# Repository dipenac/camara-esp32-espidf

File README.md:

# Proyecto vision artifical - ESP32CAM

 ## Instrucciones de instalacion y configuracion
 En esta seccion se detalla el proceso de instalacion y configuracion de los repositorios necesarios para el manejo de un **esp32-cam** por medio de el entorno de desarrolo **ESP-IDF**, en el sistema operativo LINUX. 

 ### ESP-IDF
 La instalacion y configuracion del entorno de desarrollo se puede encontrar directamente en el repositorio del fabricante espressif ([Get started - ESPIDF](https://docs.espressif.com/projects/esp-idf/en/latest/esp32/get-started/index.html)).

 - [x] En primer lugar es necesario **clonar el repositorio** de github correspondiente de ESP-IDF.
   ```sh
   git clone --recursive https://github.com/espressif/esp-idf
   ``` 
 - [x] Una vez clonado el repositorio es necesario dirigirse a la carpeta.
   ```sh
   cd ~/esp-idf
   ```
 - [x] Es necesario ejecutar el archivo bash **install.sh**, para poder utilizar las funciones de ESP-IDF.
   ```sh
   ./install.sh
   ``` 
 - [x] Luego se ejecuta el archivo bash **export.sh**, para exportar las variables de entorno que se utilizaran.
   ```sh
   . ./export.sh
   ```
En este punto el entorno de desarrollo ESP-IDF debe estar configurado y listo para implementar proyectos sobre un esp32.

 ### Driver para esp32-cam 
  La instalacion y configuracion del driver se puede encontrar directamente en el repositorio del fabricante espressif ([ESP32 Camera Driver](https://github.com/espressif/esp32-camera)).

 - [x] En primer lugar es necesario **clonar el repositorio** de github correspondiente del driver esp32-cam. Es necesario clonar el repositorio en la carpeta *components* del repositorio clonado de ESP-IDF.
   ```sh
   cd ~/esp-idf/components
   git clone --recursive https://github.com/espressif/esp32-camera
   ``` 
 - [x] Una vez clonado el repositorio en la carpeta correspondiente, se procede a [crear un proyecto](#crear-un-proyecto-esp-idf) en ESP-IDF. Una vez creado el proeycto es necesario realizar los ajustes necesarios para que el driver de la camara funcione junto con el esp32-cam, referirse a [inicializacion camara con esp32](#inicializacion-camara-con-esp32).
    ```c
    #include <esp_camera.h>
    ```

 ## Implementacion
 
 ### Crear un proyecto ESP-IDF para esp32
 El entorno de desarrollo ESP-IDF permite realizar varias acciones por medio de el archivo ***idf.py***. En este caso mostraremos un pequeno instructivo para registrar como **crear, construir y ejecutar** un proyecto en esp-32.

 - [x] En primer lugar es recomendable crear una carpeta en donde se puedan alojar todos los proyectos que se vayan a realizar.

    ```sh
    mkdir ~/esp-idf/projects
    ```
 - [x] Y dentro del folder de *projects* utilizamos una de las funciones que presta ***idf.py***, con la cual creamos un projecto con el nombre que deseemos.

    ```sh
    cd ~/esp-idf/projects
    idf.py create-project "nombre-del-proyecto"
    ```
    ```sh
    Ejemplo: idf.py create-project helloworld
    ```
      > Todas las funciones que presta ***idf.py*** se pueden observar ejecutando el siguiente comando.

      ```sh
        idf.py --help
      ```

 - [x] Lo siguiente es ingresar al folder del proyecto, y establecer el microcontrolador que estamos usando (en este caso el esp32cam corresponde a un esp32).

    ```sh
    cd helloworld
    idf.py set-target esp32
    ```
    > Todos los microcontroladores disponibles se pueden visualizar con el siguiente comando.
    ```sh
    idf.py set-target --help
    ```
 - [X] Una vez establecido el microcontrolador se construye el proyecto para importar todas las dependencias necesarias para manejar el esp32 que estamos usando.
    ```sh
    idf.py build
    ```
Lo siguiente es desarrollar nuestros proyectos e importar las librerias necesarias para el manejo de los perifericos integrados en el microcontrolador.

### Inicializacion camara con esp32
 Antes de utilizar el driver de la camara, debemos hacer uso del modulo PSRAM externo con el que cuenta el esp32cam. Asi como ajustar la frecuencia de la memoria FLASH y PSRAM a 80 MHz.
  - [X] Dirigirse a la ubicacion del proyecto y ejecutar el siguiente comando para realziar las configuraciones.
    ```sh
    idf.py menuconfig
    ```
  - [X] Esto abrira un entorno grafico por terminal que permitira cambiar el archivo **sdkconfig**.
  
    * **Cambiar frecuencia memoria FLASH**

    * **Habilitar la PSRAM externa y cambiar frecuencia SPRAM**.

Con estas configuraciones ya es posible utilizar la camara y la PSRAM externa con la que cuenta el esp32.
```c
#include <esp_camera.h>
```

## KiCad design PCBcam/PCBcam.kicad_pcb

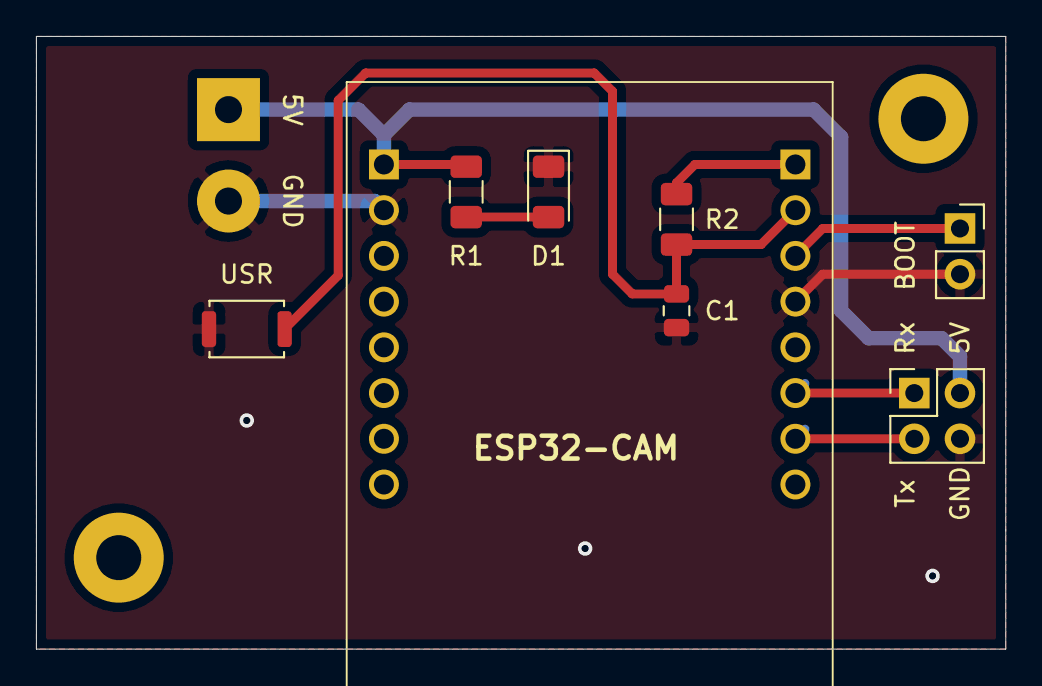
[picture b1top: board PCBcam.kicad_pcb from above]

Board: 2 copper layers, 53.8 x 34.0 mm, 9 parts (0 on the bottom side), 8 nets.

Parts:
BT1: USR; SW_Push_SPST_NO_Alps_SKRK
C1: 1uF; C_0805_2012Metric
D1: LED; LED_1206_3216Metric
ESP32-CAM: ESP32-CAM; ESP32CAM
J1: Rx/Tx; PinSocket_2x02_P2.54mm_Vertical
J2: Conn_01x02; PinSocket_1x02_P2.54mm_Vertical
J3: 5V-Gnd; SolderWirePad_1x02_P5.08mm_Drill1.5mm
R1: 1k; R_1206_3216Metric
R2: 10k; R_1206_3216Metric

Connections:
3v3: ESP32-CAM.9, R2.1
5v: ESP32-CAM.8, J1.3, J3.1, R1.1
unnamed: D1.2, R1.2
gnd: BT1.1, C1.2, D1.1, ESP32-CAM.7, ESP32-CAM.12, J1.4, J2.2, J3.2
i0: ESP32-CAM.11, J2.1
rx: ESP32-CAM.14, J1.1
tx: ESP32-CAM.15, J1.2
usr: BT1.2, C1.1, ESP32-CAM.10, R2.2

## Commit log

2022-10-07 chore(main): folders created
2022-10-07 feat(main): files created
2022-10-07 chore(main): cleaning up
2022-10-08 chore(main): README updated
2022-10-08 chore(main): img added and README updated
2022-10-08 chore(main): update
2022-11-01 chore(PCB): PCB layout added
2022-11-02 feat(src): commucation developement
2022-11-06 feat(src/test): communication tests done
2022-11-06 feat(src): communication tool done
2022-11-07 feat(comms): README updated
2022-12-08 feat(src):code upload
2022-12-08 feat(src):code uploaded
2022-12-08 feat(src):sdkconfig upload
2022-12-08 feat(src): take_picture update
2022-12-08 feat(scr): take_picture_update2
2022-12-09 Feat(process)
    Convertion JPG 2 RGB
2022-12-09 feat(take_picture): README created and updated
